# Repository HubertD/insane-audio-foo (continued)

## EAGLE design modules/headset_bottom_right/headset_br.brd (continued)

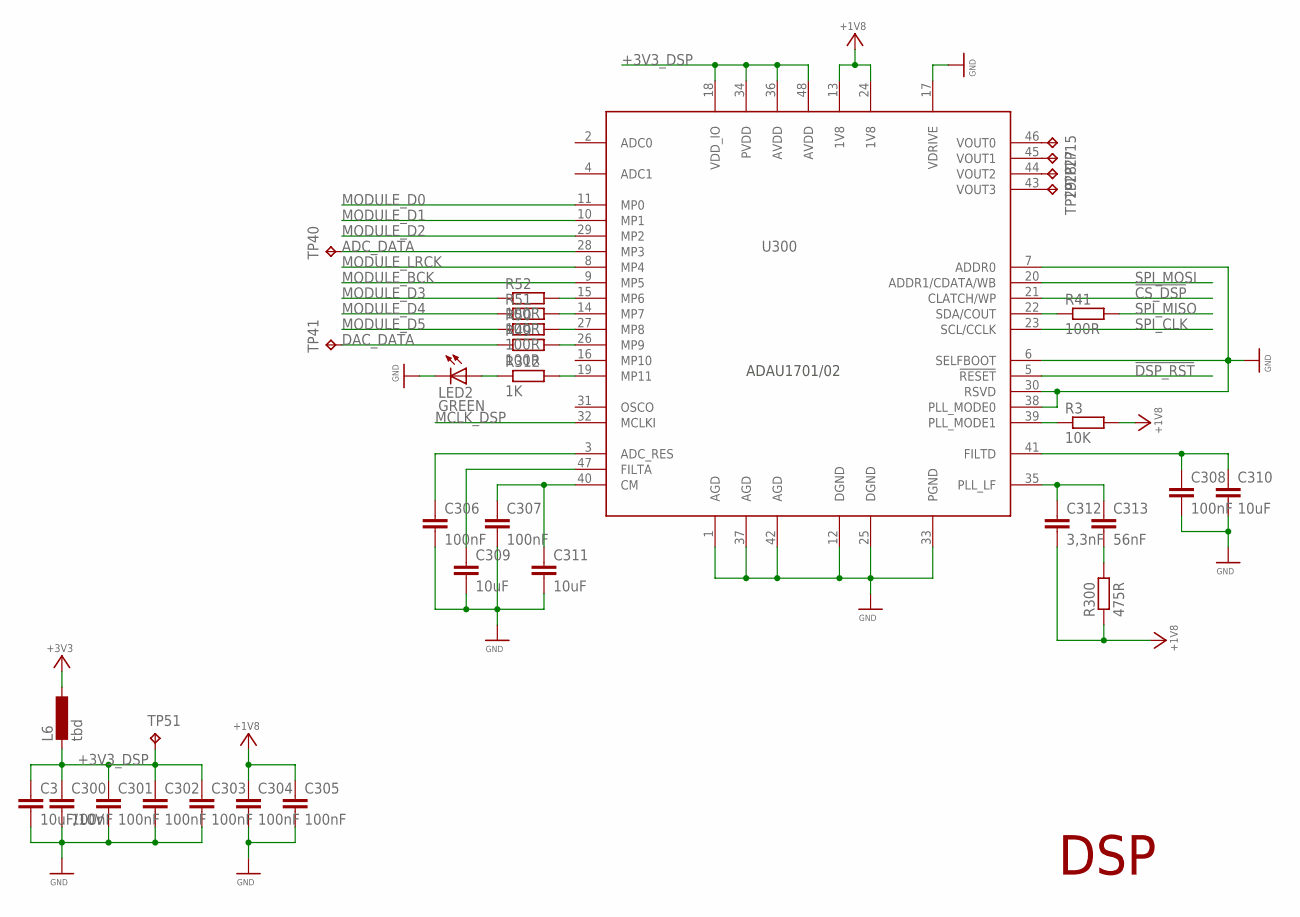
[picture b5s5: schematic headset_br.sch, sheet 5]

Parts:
C3: 10uF/10V; C0805; MPN C2012X7R1A106K125AC
C300, C301, C302, C303, C304, C305, C306, C307, C308: 100nF; C0603; MPN 0603YC104KAT2A
C309, C310, C311: 10uF; C1206; MPN C1206C106K4RACTU
C312: 3,3nF; C0603; MPN C0603C332K5RACTU
C313: 56nF; C0603; MPN VJ0603Y563KXJPW1BC
L6: tbd; R0805
LED2: GREEN; CHIP-LED0603
R3: 10K; R0603; MPN ERJ-3EKF1002V
R41, R49, R50, R51, R52: 100R; R0603; MPN ERJ-3EKF1000V
R300: 475R; R0603; MPN ERJ-3EKF4750V
R312: 1K; R0603; MPN CRCW06031K00FKEA
TP15, TP27, TP28, TP29: TPXS; TESTPAD_EXTRA_SMALL
TP40, TP41, TP51: TPS; TESTPAD_SMALL
U300: ADAU1701/02ADAU1701JSTZ; LQFP48

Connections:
!CS_DSP: U300.21 (CLATCH/WP); also elsewhere on the board
!DSP_RST: U300.5 (!RESET); also elsewhere on the board
+1V8: C304.1, C305.1, C312.2, R3.2, R300.1, U300.13 (1V8), U300.24 (1V8); also elsewhere on the board
+3V3: L6.1; also elsewhere on the board
+3V3_DSP: C3.1, C300.1, C301.1, C302.1, C303.1, L6.2, TP51.P$1, U300.18 (VDD_IO), U300.34 (PVDD), U300.36 (AVDD), U300.48 (AVDD)
ADC_DATA: TP40.P$1, U300.28 (MP3); also elsewhere on the board
DAC_DATA: R49.1, TP41.P$1; also elsewhere on the board
GND: C3.2, C300.2, C301.2, C302.2, C303.2, C304.2, C305.2, C306.2, C307.2, C308.2, C309.2, C310.2, C311.2, LED2.C, U300.1 (AGD), U300.6 (SELFBOOT), U300.7 (ADDR0), U300.12 (DGND), U300.17 (VDRIVE), U300.25 (DGND), U300.30 (RSVD), U300.33 (PGND), U300.37 (AGD), U300.38 (PLL_MODE0), U300.42 (AGD); also elsewhere on the board
MCLK_DSP: U300.32 (MCLKI); also elsewhere on the board
MODULE_BCK: U300.9 (MP5); also elsewhere on the board
MODULE_D0: U300.11 (MP0); also elsewhere on the board
MODULE_D1: U300.10 (MP1); also elsewhere on the board
MODULE_D2: U300.29 (MP2); also elsewhere on the board
MODULE_D3: R52.1; also elsewhere on the board
MODULE_D4: R51.1; also elsewhere on the board
MODULE_D5: R50.1; also elsewhere on the board
MODULE_LRCK: U300.8 (MP4); also elsewhere on the board
unnamed: C312.1, C313.1, U300.35 (PLL_LF)
unnamed: C313.2, R300.2
unnamed: C307.1, C311.1, U300.40 (CM)
unnamed: C308.1, C310.1, U300.41 (FILTD)
unnamed: C309.1, U300.47 (FILTA)
unnamed: C306.1, U300.3 (ADC_RES)
unnamed: R312.2, U300.19 (MP11)
unnamed: LED2.A, R312.1
unnamed: R3.1, U300.39 (PLL_MODE1)
unnamed: TP15.P$1, U300.46 (VOUT0)
unnamed: TP27.P$1, U300.45 (VOUT1)
unnamed: TP28.P$1, U300.44 (VOUT2)
unnamed: TP29.P$1, U300.43 (VOUT3)
unnamed: R41.1, U300.22 (SDA/COUT)
unnamed: R52.2, U300.15 (MP6)
unnamed: R51.2, U300.14 (MP7)
unnamed: R50.2, U300.27 (MP8)
unnamed: R49.2, U300.26 (MP9)
SPI_CLK: U300.23 (SCL/CCLK); also elsewhere on the board
SPI_MISO: R41.2; also elsewhere on the board
SPI_MOSI: U300.20 (ADDR1/CDATA/WB); also elsewhere on the board

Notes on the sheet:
DSP

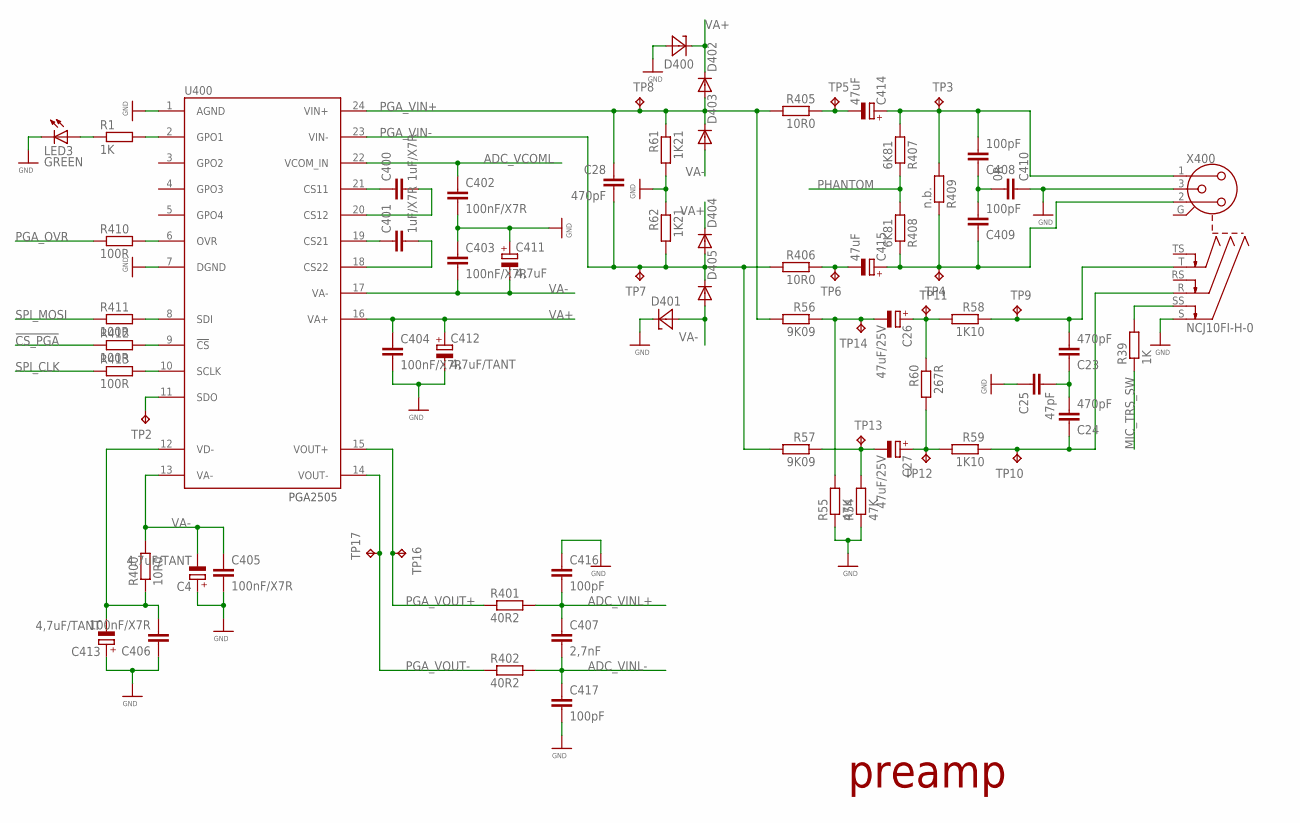
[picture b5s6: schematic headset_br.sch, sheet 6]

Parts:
C4, C412, C413: 4,7uF/TANT; SMC_B; MPN TAJB475K020RNJ
C23, C24, C28: 470pF; C0603; MPN CGA3E1X7R1C474K080AC
C25: 47pF; C0603; MPN C0603C0G1H470J030BA
C26, C27: 47uF/25V; PANASONIC_FK_V_SIZE_D; MPN EEE-FK1E470P
C400, C401: 1uF/X7R; C0603; MPN C1608X7R1C105K080AC
C402, C403, C404, C405, C406: 100nF/X7R; C0603; MPN 0603YC104KAT2A
C407: 2,7nF; C0603; MPN GRM033R61A272KA01D
C408, C409, C416, C417: 100pF; C0603; MPN 06035A101JAT2A
C410: 0R; C0603
C411: 4,7uF; SMC_B; MPN TAJB475K020RNJ
C414, C415: 47uF; PANASONIC_FK_V_SIZE_F; MPN EEEFK1J470P
D400, D401: D-ZENERDO-214AC; DO214AC; MPN BZG05C5V6TR
D402, D403, D404, D405: MBRA120ET3G; SMA
LED3: GREEN; CHIP-LED0603
R1, R39: 1K; R0603; MPN CRCW06031K00FKEA
R54, R55: 47K; R0603; MPN ERJ-3EKF4702V
R56, R57: 9K09; R1206; MPN TNPW12069K09BEEA
R58, R59: 1K10; R1206; MPN ERJ-8ENF1101V
R60: 267R; R1206; MPN ERJ-8ENF2670V
R61, R62: 1K21; R0805; MPN ERA-6AEB1211V
R400, R405, R406: 10R0; R1206; MPN CRT1206-BY-10R0ELF
R401, R402: 40R2; R0805; MPN PHP00805E40R2BST1
R407, R408: 6K81; R1206; MPN TNPW12066K81BEEN
R409: n.b.; R0805
R410, R411, R412, R413: 100R; R0603; MPN ERJ-3EKF1000V
TP2, TP16, TP17: TPS; TESTPAD_SMALL
TP3, TP4, TP5, TP6, TP7, TP8, TP9, TP10, TP11, TP12, TP13, TP14: TP; TESTPAD
U400: PGA2505; SSOP24
X400: NCJ10FI-H-0

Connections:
!CS_PGA: R412.1; also elsewhere on the board
ADC_VCOML: C402.1, U400.22 (VCOM_IN); also elsewhere on the board
ADC_VINL+: C407.1, C416.2, R401.2; also elsewhere on the board
ADC_VINL-: C407.2, C417.1, R402.2; also elsewhere on the board
GND: C4.+, C25.1, C402.2, C403.1, C404.2, C405.2, C406.1, C410.1, C411.+, C412.-, C413.+, C416.1, C417.2, D400.A, D401.C, LED3.C, R54.1, R55.1, R61.2, R62.1, U400.1 (AGND), U400.7 (DGND), X400.3, X400.S; also elsewhere on the board
MIC_TRS_SW: R39.1; also elsewhere on the board
unnamed: C408.1, C409.2, C410.2
unnamed: C414.M (-), R405.1, TP5.P$1
unnamed: C415.M (-), R406.1, TP6.P$1
unnamed: C400.1, U400.21 (CS11)
unnamed: C400.2, U400.20 (CS12)
unnamed: C406.2, C413.-, R400.1, U400.12 (VD-)
unnamed: C401.1, U400.19 (CS21)
unnamed: C401.2, U400.18 (CS22)
unnamed: R1.2, U400.2 (GPO1)
unnamed: LED3.A, R1.1
unnamed: R410.2, U400.6 (OVR)
unnamed: R411.2, U400.8 (SDI)
unnamed: R412.2, U400.9 (!CS)
unnamed: R413.2, U400.10 (SCLK)
unnamed: TP2.P$1, U400.11 (SDO)
unnamed: R39.2, X400.SS
unnamed: C23.1, C24.2, C25.2
unnamed: C27.P (+), R59.2, R60.2, TP12.P$1
unnamed: C23.2, R58.1, TP9.P$1, X400.T
unnamed: C24.1, R59.1, TP10.P$1, X400.R
unnamed: C27.N (-), R54.2, R57.1, TP13.P$1
unnamed: C26.N (-), R55.2, R56.1, TP14.P$1
unnamed: C26.P (+), R58.2, R60.1, TP11.P$1
PGA_OVR: R410.1; also elsewhere on the board
PGA_VIN+: C28.1, D402.A, D403.C, R56.2, R61.1, R405.2, TP8.P$1, U400.24 (VIN+)
PGA_VIN-: C28.2, D404.A, D405.C, R57.2, R62.2, R406.2, TP7.P$1, U400.23 (VIN-)
PGA_VOUT+: R401.1, TP16.P$1, U400.15 (VOUT+)
PGA_VOUT-: R402.1, TP17.P$1, U400.14 (VOUT-)
PHANTOM: R407.1, R408.2; also elsewhere on the board
SPI_CLK: R413.1; also elsewhere on the board
SPI_MOSI: R411.1; also elsewhere on the board
VA+: C404.1, C412.+, D400.C, D402.C, D404.C, U400.16 (VA+); also elsewhere on the board
VA-: C4.-, C403.2, C405.1, C411.-, D401.A, D403.A, D405.A, R400.2, U400.13 (VA-), U400.17 (VA-); also elsewhere on the board
VIN+: C408.2, C414.P (+), R407.2, R409.2, TP3.P$1, X400.1
VIN-: C409.1, C415.P (+), R408.1, R409.1, TP4.P$1, X400.2

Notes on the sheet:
preamp

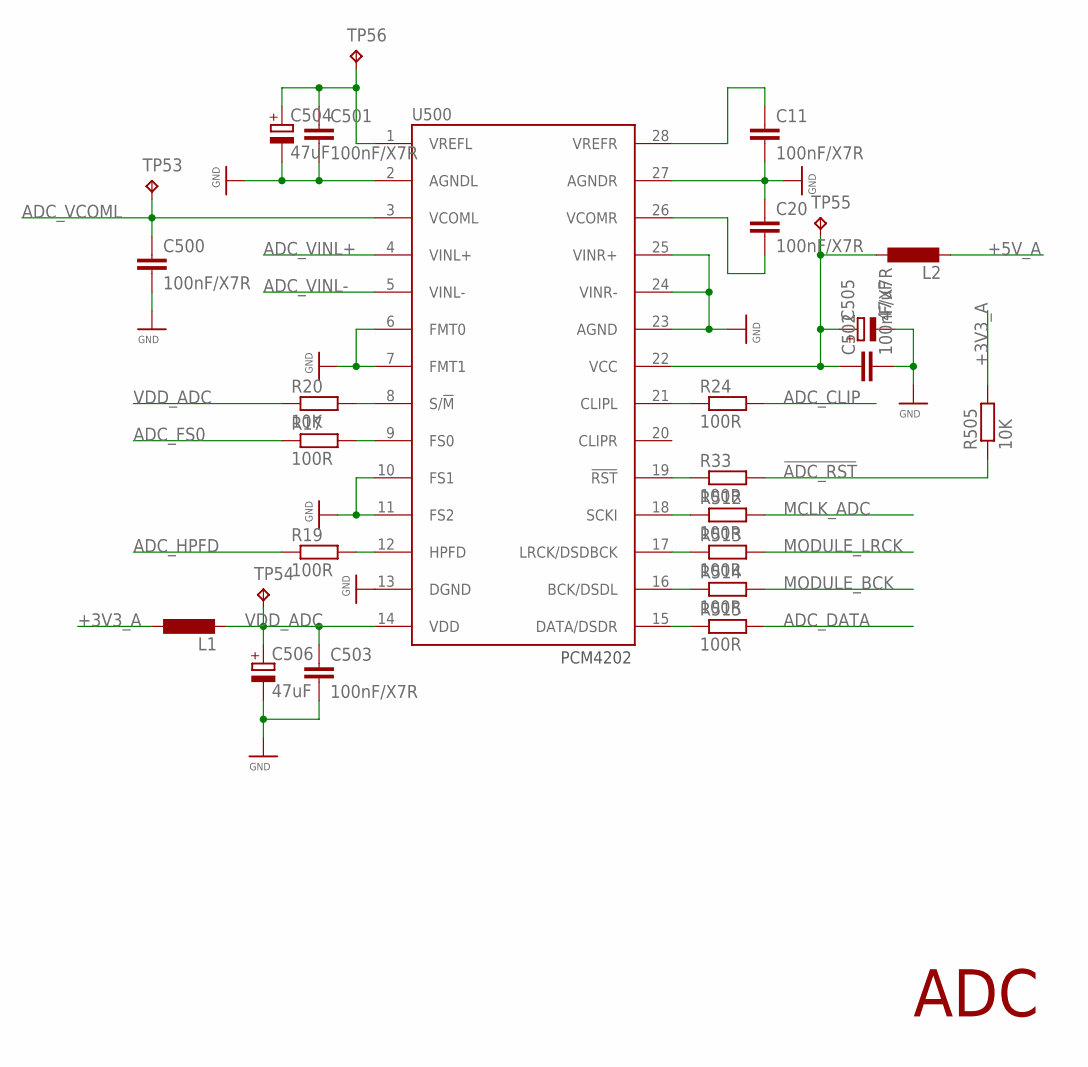
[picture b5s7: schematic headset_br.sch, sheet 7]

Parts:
C11, C20, C500, C501, C502, C503: 100nF/X7R; C0603; MPN 0603YC104KAT2A
C504: 47uF; VISHAY_TR3_SIZE_B; MPN TR3B476K010C0350
C505, C506: 47uF; KEMET_EDK_5MM; MPN EDK476M010A9DAA
L1, L2: L0805; R0805
R17, R19, R24, R33, R512, R513, R514, R515: 100R; R0603; MPN ERJ-3EKF1000V
R20, R505: 10K; R0603; MPN ERJ-3EKF1002V
TP53, TP54, TP55, TP56: TPS; TESTPAD_SMALL
U500: PCM4202; SSOP28

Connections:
!ADC_RST: R33.2, R505.1; also elsewhere on the board
+3V3_A: L1.1, R505.2; also elsewhere on the board
+5V_A: L2.2; also elsewhere on the board
ADC_CLIP: R24.2; also elsewhere on the board
ADC_DATA: R515.2; also elsewhere on the board
ADC_FS0: R17.1; also elsewhere on the board
ADC_HPFD: R19.1; also elsewhere on the board
ADC_VCOML: C500.1, TP53.P$1, U500.3 (VCOML); also elsewhere on the board
ADC_VINL+: U500.4 (VINL+); also elsewhere on the board
ADC_VINL-: U500.5 (VINL-); also elsewhere on the board
GND: C11.2, C20.1, C500.2, C501.2, C502.2, C503.2, C504.M (-), C505.M (-), C506.M (-), U500.2 (AGNDL), U500.6 (FMT0), U500.7 (FMT1), U500.10 (FS1), U500.11 (FS2), U500.13 (DGND), U500.23 (AGND), U500.24 (VINR-), U500.25 (VINR+), U500.27 (AGNDR); also elsewhere on the board
MCLK_ADC: R512.2; also elsewhere on the board
MODULE_BCK: R514.2; also elsewhere on the board
MODULE_LRCK: R513.2; also elsewhere on the board
unnamed: C501.1, C504.P (+), TP56.P$1, U500.1 (VREFL)
unnamed: C502.1, C505.P (+), L2.1, TP55.P$1, U500.22 (VCC)
unnamed: R17.2, U500.9 (FS0)
unnamed: R512.1, U500.18 (SCKI)
unnamed: R513.1, U500.17 (LRCK/DSDBCK)
unnamed: R514.1, U500.16 (BCK/DSDL)
unnamed: R515.1, U500.15 (DATA/DSDR)
unnamed: R19.2, U500.12 (HPFD)
unnamed: R20.2, U500.8 (S/!M)
unnamed: R24.1, U500.21 (CLIPL)
unnamed: C20.2, U500.26 (VCOMR)
unnamed: C11.1, U500.28 (VREFR)
unnamed: R33.1, U500.19 (!RST)
VDD_ADC: C503.1, C506.P (+), L1.2, R20.1, TP54.P$1, U500.14 (VDD)

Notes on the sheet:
ADC

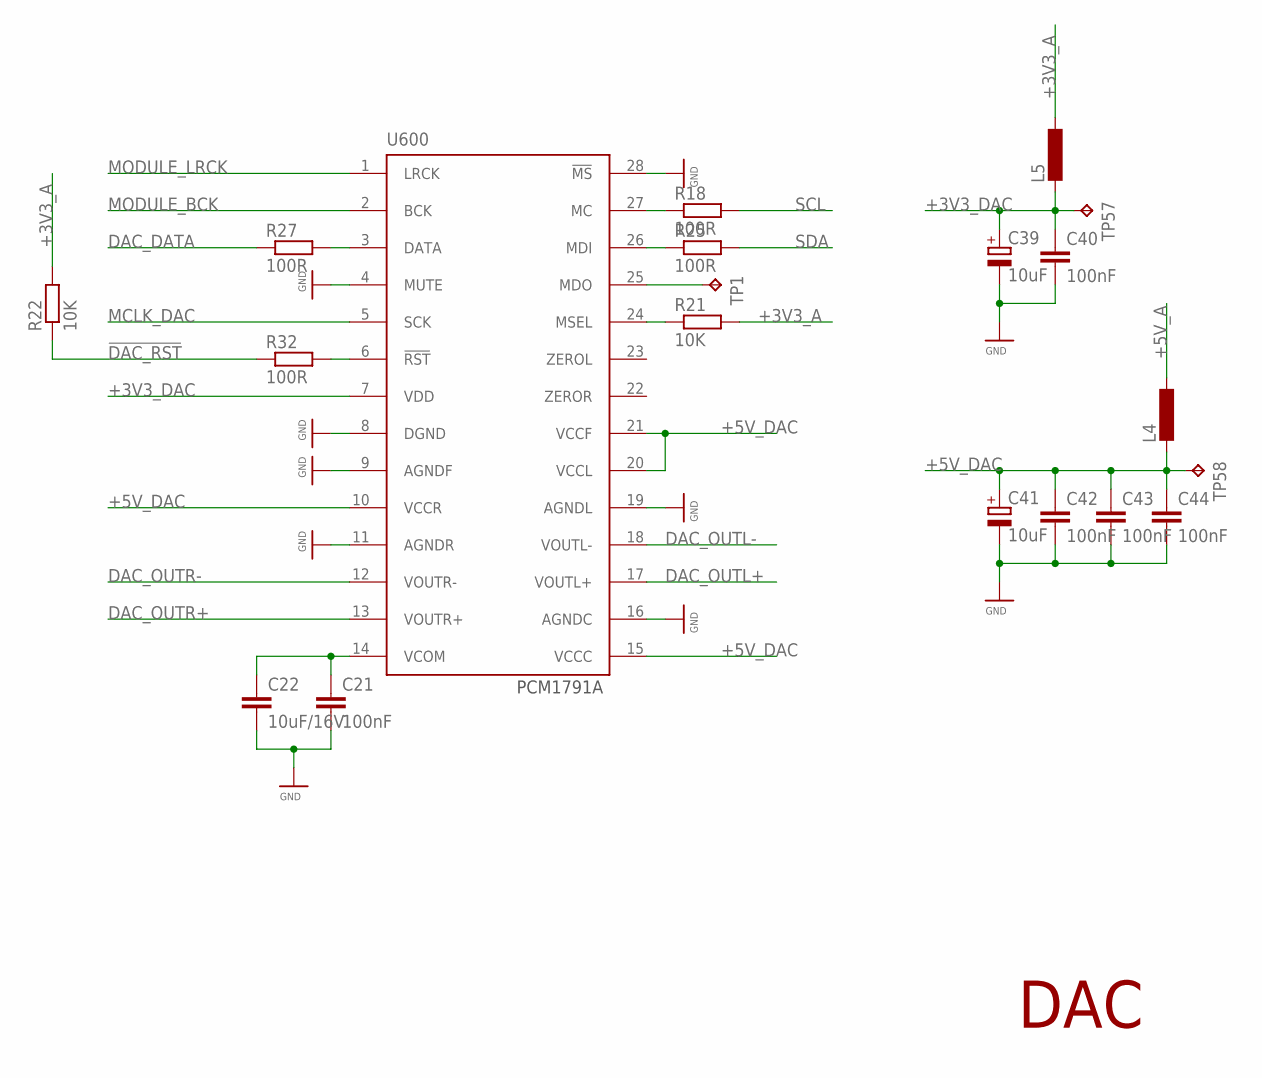
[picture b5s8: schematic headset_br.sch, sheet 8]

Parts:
C21, C40, C42, C43, C44: 100nF; C0603; MPN 0603YC104KAT2A
C22: 10uF/16V; C1206; MPN C1206C106K4RACTU
C39, C41: 10uF; SMC_A; MPN F931A106KAA
L4, L5: L0805; R0805
R18, R25, R27, R32: 100R; R0603; MPN ERJ-3EKF1000V
R21, R22: 10K; R0603; MPN ERJ-3EKF1002V
TP1, TP57, TP58: TPS; TESTPAD_SMALL
U600: PCM1791A; SSOP28

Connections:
!DAC_RST: R22.1, R32.1; also elsewhere on the board
+3V3_A: L5.1, R21.2, R22.2; also elsewhere on the board
+3V3_DAC: C39.+, C40.1, L5.2, TP57.P$1, U600.7 (VDD)
+5V_A: L4.1; also elsewhere on the board
+5V_DAC: C41.+, C42.1, C43.1, C44.1, L4.2, TP58.P$1, U600.10 (VCCR), U600.15 (VCCC), U600.20 (VCCL), U600.21 (VCCF)
DAC_DATA: R27.1; also elsewhere on the board
DAC_OUTL+: U600.17 (VOUTL+); also elsewhere on the board
DAC_OUTL-: U600.18 (VOUTL-); also elsewhere on the board
DAC_OUTR+: U600.13 (VOUTR+); also elsewhere on the board
DAC_OUTR-: U600.12 (VOUTR-); also elsewhere on the board
GND: C21.2, C22.2, C39.-, C40.2, C41.-, C42.2, C43.2, C44.2, U600.4 (MUTE), U600.8 (DGND), U600.9 (AGNDF), U600.11 (AGNDR), U600.16 (AGNDC), U600.19 (AGNDL), U600.28 (!MS); also elsewhere on the board
MCLK_DAC: U600.5 (SCK); also elsewhere on the board
MODULE_BCK: U600.2 (BCK); also elsewhere on the board
MODULE_LRCK: U600.1 (LRCK); also elsewhere on the board
unnamed: TP1.P$1, U600.25 (MDO)
unnamed: C21.1, C22.1, U600.14 (VCOM)
unnamed: R21.1, U600.24 (MSEL)
unnamed: R18.1, U600.27 (MC)
unnamed: R25.1, U600.26 (MDI)
unnamed: R27.2, U600.3 (DATA)
unnamed: R32.2, U600.6 (!RST)
SCL: R18.2; also elsewhere on the board
SDA: R25.2; also elsewhere on the board

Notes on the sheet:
DAC

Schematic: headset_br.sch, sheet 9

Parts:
C900, C908, C910, C911: 220p/NP0/50V/5%; C0603; MPN C0603C221J5GACTU
C904, C905, C906, C907: 2,2uF/10V; C0603; MPN C1608X7R1A225K080AC
C916, C917, C918: 1uF; C0603; MPN C1608X7R1C105K080AC
C919: 2,2uF; C0603; MPN C1608X7R1A225K080AC
C920, C921: 270pf/n.b.; C0603
L3: tbd; R0805
R900, R901, R902, R903: 20K/1%; R0603; MPN ERJ-3EKF2002V
R912: 10K; R0603; MPN ERJ-3EKF1002V
R913, R914, R915: 100R; R0603; MPN ERJ-3EKF1000V
R922, R923: 0R; R0603
R924: 1K; R0603; MPN CRCW06031K00FKEA
TP30, TP59: TPS; TESTPAD_SMALL
U700: TPA6130A2; TPA6130A2-QFN
X700: NMJ6HHD2

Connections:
!HPA_SD: R912.2, R913.1; also elsewhere on the board
+3V3_A: TP30.P$1; also elsewhere on the board
+5V_A: L3.1; also elsewhere on the board
DAC_OUTL+: R901.1; also elsewhere on the board
DAC_OUTL-: R900.1; also elsewhere on the board
DAC_OUTR+: R902.1; also elsewhere on the board
DAC_OUTR-: R903.1; also elsewhere on the board
GND: C900.2, C908.2, C910.2, C911.2, C916.2, C917.2, C919.1, C920.2, C921.2, R912.1, U700.P3 (GND), U700.P9 (GND), U700.P10 (GND), U700.P13 (GND), U700.P19 (GND), U700.POWERPAD (GND), X700.S; also elsewhere on the board
HPA_LIN+: C905.1, C910.1, R901.2
HPA_LIN-: C904.1, C911.1, R900.2
HPA_RIN+: C900.1, C906.1, R902.2
HPA_RIN-: C907.1, C908.1, R903.2
HPA_TRS_SW: R924.1; also elsewhere on the board
unnamed: C918.1, U700.P18 (CPP)
unnamed: C918.2, U700.P17 (CPM)
unnamed: C919.2, U700.P15 (CPVSS), U700.P16 (CPVSS)
unnamed: C907.2, U700.P5 (RINM)
unnamed: C906.2, U700.P4 (RINP)
unnamed: C905.2, U700.P2 (LINP)
unnamed: C904.2, U700.P1 (LINM)
unnamed: R922.1, U700.P14 (HPL)
unnamed: C921.1, R922.2, X700.T
unnamed: R923.1, U700.P11 (HPR)
unnamed: C920.1, R923.2, X700.R
unnamed: R914.2, U700.P7 (SDA)
unnamed: R915.2, U700.P8 (SCL)
unnamed: R913.2, U700.P6 (!SD)
unnamed: R924.2, X700.SN
unnamed: C916.1, C917.1, L3.2, TP59.P$1, U700.P12 (VDD), U700.P20 (VDD)
SCL: R915.1; also elsewhere on the board
SDA: R914.1; also elsewhere on the board

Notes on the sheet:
Headphone Amp
may be removed if DAC output voltage does not exceed +/- 3V

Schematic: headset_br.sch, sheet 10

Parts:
C1000: 1uF; C0603; MPN C1608X7R1C105K080AC
MODULE_CON: PCIE-36-EDGE
R1001, R1002, R1003: 22R; R0603; MPN ERJ-3EKF22R0V
TP36, TP1000, TP1001, TP1002, TP1004, TP1006, TP1007, TP1008, TP1009: TPS; TESTPAD_SMALL
TP1003: TPXS; TESTPAD_EXTRA_SMALL
U1: CDCLVC1103; TSSOP8

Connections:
!MODULE_SPI_CS: MODULE_CON.A14; also elsewhere on the board
+3V3: C1000.1, U1.2 (1G), U1.6 (VDD); also elsewhere on the board
GND: C1000.2, MODULE_CON.A1, MODULE_CON.A6, MODULE_CON.A8, MODULE_CON.A12, MODULE_CON.A17, MODULE_CON.B1, MODULE_CON.B6, MODULE_CON.B7, MODULE_CON.B8, MODULE_CON.B12, MODULE_CON.B17, U1.4 (GND); also elsewhere on the board
MCLK_ADC: R1002.2; also elsewhere on the board
MCLK_DAC: R1001.2; also elsewhere on the board
MCLK_DSP: R1003.2; also elsewhere on the board
MODULE_+3V3: MODULE_CON.A18; also elsewhere on the board
MODULE_+5V: MODULE_CON.B18; also elsewhere on the board
MODULE_+6V: MODULE_CON.B9; also elsewhere on the board
MODULE_+12V: MODULE_CON.A11
MODULE_+16V: MODULE_CON.B10
MODULE_+49V: MODULE_CON.B11, TP1009.P$1; also elsewhere on the board
MODULE_-6V: MODULE_CON.A9; also elsewhere on the board
MODULE_-16V: MODULE_CON.A10
MODULE_BCK: MODULE_CON.B5, TP1001.P$1; also elsewhere on the board
MODULE_BOOTLDR: MODULE_CON.B16; also elsewhere on the board
MODULE_D0: MODULE_CON.A4, TP1003.P$1; also elsewhere on the board
MODULE_D1: MODULE_CON.B4, TP1004.P$1; also elsewhere on the board
MODULE_D2: MODULE_CON.A3, TP36.P$1; also elsewhere on the board
MODULE_D3: MODULE_CON.B3, TP1006.P$1; also elsewhere on the board
MODULE_D4: MODULE_CON.A2, TP1007.P$1; also elsewhere on the board
MODULE_D5: MODULE_CON.B2, TP1008.P$1; also elsewhere on the board
MODULE_LRCK: MODULE_CON.A5, TP1002.P$1; also elsewhere on the board
MODULE_MCLK: MODULE_CON.A7, TP1000.P$1, U1.1 (CLKIN)
MODULE_RESET: MODULE_CON.A16; also elsewhere on the board
MODULE_SPI_MISO: MODULE_CON.B13; also elsewhere on the board
MODULE_SPI_MOSI: MODULE_CON.A13; also elsewhere on the board
MODULE_SPI_SCK: MODULE_CON.B14; also elsewhere on the board
MODULE_UART_RX: MODULE_CON.A15; also elsewhere on the board
MODULE_UART_TX: MODULE_CON.B15; also elsewhere on the board
unnamed: R1001.1, U1.3 (Y0)
unnamed: R1002.1, U1.8 (Y1)
unnamed: R1003.1, U1.5 (Y2)

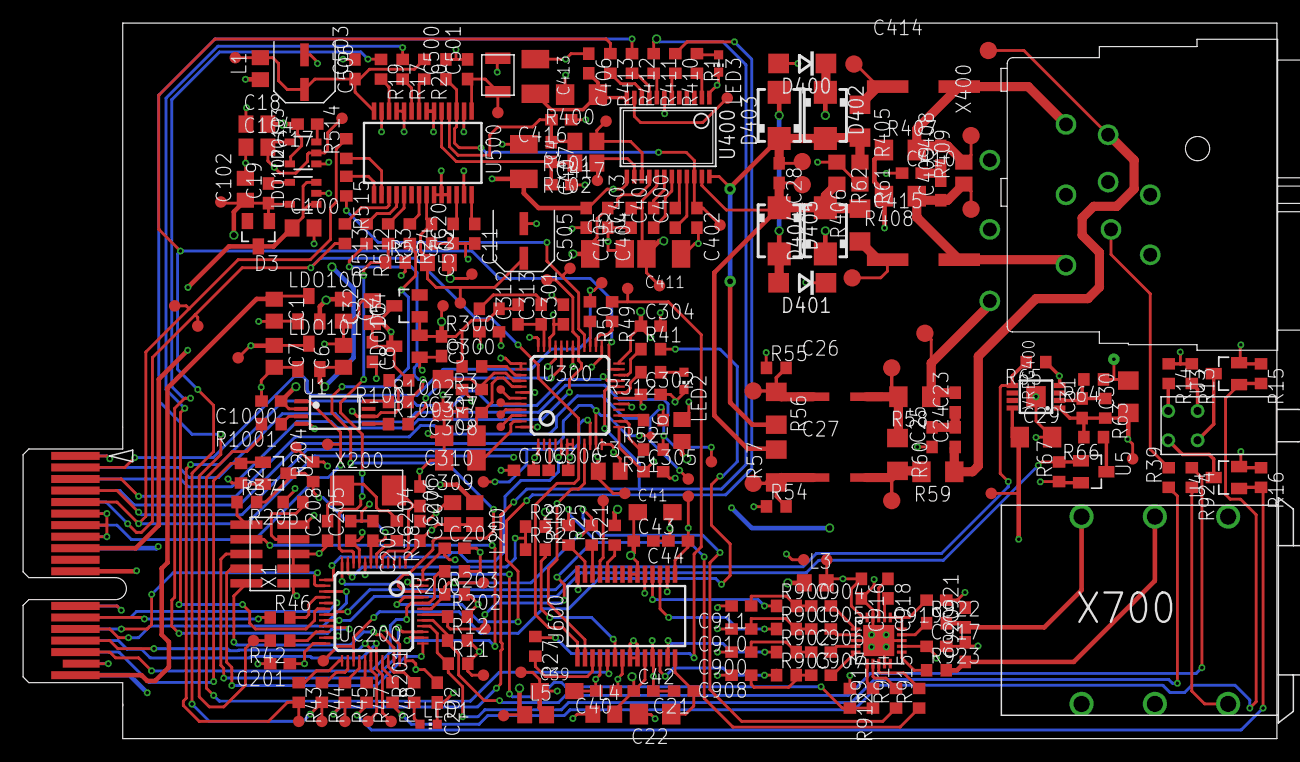
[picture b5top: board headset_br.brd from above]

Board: 4 copper layers, 108.6 x 62.0 mm, 287 parts (0 on the bottom side), 185 nets.

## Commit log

2014-03-24 initial checkin
2014-03-25 added attributes to build a usable BOM
